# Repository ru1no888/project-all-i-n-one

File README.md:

# ระบบอุปกรณ์สวมใส่ติดตามสัญญาณชีพสุขภาพและเว็บแอปพลิเคชันบริหารจัดการคิวผู้ป่วยนอก
### (Hospital Queue Patient Portal & Smartwatch Health Monitoring)

---

## 📌 บทนำและภาพรวมโครงงาน (Overview)
โครงงานนี้เป็นการวิจัยและพัฒนานวัตกรรมระบบอุปกรณ์สวมใส่อัจฉริยะ (Smartwatch) ร่วมกับเว็บแอปพลิเคชันบริหารจัดการคิวผู้ป่วยนอกของโรงพยาบาล เพื่อยกระดับความปลอดภัยของผู้ป่วยในระหว่างรอรับการตรวจรักษา โดยระบบสามารถ:
1. **ติดตามสัญญาณชีพแบบเรียลไทม์ (Continuous Vital Signs Monitoring):** วัดอัตราการเต้นของหัวใจ (Heart Rate) และระดับความอิ่มตัวของออกซิเจนในเลือด ($SpO_2$) พร้อมคำนวณดัชนีช็อก (Shock Index: $SI = \frac{HR}{SBP}$) เพื่อประเมินภาวะวิกฤตของผู้ป่วย
2. **ตรวจจับอุบัติเหตุการหกล้ม (Multi-Stage Fall Detection):** ตรวจจับสภาวะการตกอิสระ (Free-fall), แรงกระแทก (Impact $SVM > 2.5g$) และสภาวะแน่นิ่งผิดปกติ (Inactivity) ด้วยเซนเซอร์ IMU 6 แกน
3. **จัดลำดับความเร่งด่วนของคิวอัตโนมัติ (Dynamic Queue Prioritization):** คัดกรองและปรับลำดับคิวผู้ป่วยตามหลักเกณฑ์ฉุกเฉิน ESI Version 4 ผ่านระบบ AI Triage เมื่อพบสัญญาณชีพวิกฤต
4. **แจ้งเตือนและส่งข้อมูลแบบทันที (Realtime Communication):** ส่งสัญญาณเตือนไปยังห้องพยาบาลและบุคลากรทางการแพทย์ผ่าน WebSockets ทันทีที่มีเหตุฉุกเฉิน

---

## 📁 โครงสร้างโฟลเดอร์ภายในโปรเจกต์ (Repository Structure)

```text
├── 01_เล่มรายงานโครงงาน_Thesis/
│   ├── เล่มรายงานโครงงาน_ฉบับสมบูรณ์_FINAL_v3_IEEE.docx    # เล่มรายงานโครงงานฉบับสมบูรณ์ (ฟอร์แมต IEEE มทร.อีสาน ขอนแก่น)
│   ├── เล่มรายงานโครงงาน_ฉบับสมบูรณ์_FINAL_v3_IEEE.pdf     # ไฟล์ PDF เล่มสมบูรณ์ (103 หน้า พร้อมตรวจ/พิมพ์)
│   ├── ECP-P01_แบบร่างโครงงานวิศวกรรมคอมพิวเตอร์_ฉบับปรับปรุงสมบูรณ์_v14.docx # แบบร่างข้อเสนอโครงงาน (Proposal v14)
│   ├── ECP-P01_แบบร่างโครงงานวิศวกรรมคอมพิวเตอร์_ฉบับปรับปรุงสมบูรณ์_v14.pdf  # ไฟล์ PDF แบบร่างโครงงาน (20 หน้าเต็ม)
│   └── ร่างเดิมและไฟล์สำรอง_Archive/                     # โฟลเดอร์สำรองไฟล์ดราฟต์เดิมทั้งหมดอย่างปลอดภัย
│
├── 02_ฮาร์ดแวร์และวงจร_Hardware/
│   ├── smartwatch_component_pinouts.html                 # ผังการต่อสาย Pinout และวงจรเซนเซอร์แบบ Interactive Web
│   ├── component_pinouts/                                # แผนภาพ Pinout รายชิ้นส่วน
│   ├── pcb_design/                                       # ไฟล์ออกแบบแผ่นวงจรพิมพ์ PCB (KiCad / EasyEDA)
│   └── pcb_design.zip                                    # ไฟล์บีบอัดสำหรับส่งโรงงานผลิต PCB (Gerber Files)
│
├── 03_ซอร์สโค้ดและเว็บแอป_SourceCode/
│   ├── repo_README.md                                    # เอกสารคู่มือการติดตั้งและการรัน Frontend Web App
│   ├── repo_ARCHITECTURE.md                              # สถาปัตยกรรมระบบ Frontend & Backend API Spec
│   ├── repo_package.json                                 # รายการ Dependencies (Next.js 14, React, Tailwind CSS)
│   ├── repo_patient-api.ts                               # API Client Module สำหรับเชื่อมต่อระบบโรงพยาบาล
│   ├── repo_types.ts                                     # TypeScript Interface สำหรับ Patient, Queue, Vital Signs
│   └── repo_mock_backend.py                              # สคริปต์จำลองเซิร์ฟเวอร์ Mock API สำหรับการทดสอบระบบ
│
├── 04_ไฟล์ข้อมูลและเครื่องมือเสริม_Assets_Tools/
│   ├── extracted_assets/                                 # รูปภาพและกราฟิกประกอบที่ใช้ในเอกสาร
│   ├── extracted_ch4_images/                             # ภาพผลการทดลองและการทดสอบระบบในบทที่ 4
│   ├── logo/                                             # ตราสัญลักษณ์มหาวิทยาลัยเทคโนโลยีราชมงคลอีสาน
│   └── build_full_thesis.py                              # สคริปต์สำหรับบิวด์และจัดรูปแบบรูปเล่มอัตโนมัติ
│
├── AGENTS.md                                             # ข้อกำหนดและแนวทางสำหรับ AI Assistant
├── GEMINI.md                                             # กฎระเบียบข้อบังคับและ Memory Protocol ประจำโปรเจกต์
├── PROJECT_MEMORY.md                                     # บันทึกความจำระยะยาว ประวัติการพัฒนา และข้อสรุปงาน
└── README.md                                             # เอกสารภาพรวมโปรเจกต์ (ไฟล์นี้)
```

---

## 🛠️ รายละเอียดสเปกฮาร์ดแวร์และเซนเซอร์ (Hardware Specifications)

| ส่วนประกอบ (Component) | รายละเอียด (Specification) | ฟังก์ชันการทำงาน |
|---|---|---|
| **MCU Controller** | Seeed Studio XIAO ESP32-C3 | หน่วยประมวลผลหลัก รองรับ Wi-Fi 2.4GHz และ BLE 5.0 |
| **Biometric Sensor** | MAX32664 Biometric Hub + MAX30102 PPG | ตรวจวัด Pulse Rate และ $SpO_2$ ด้วยความแม่นยำสูง |
| **Motion Sensor** | MPU-6050 (6-Axis Accel + Gyro) | ตรวจจับการเคลื่อนไหวและการหกล้ม 3 ขั้นตอน (SVM Analysis) |
| **Power Management** | TP4056 + แบตเตอรี่ LiPo 3.7V (500mAh) | วงจรชาร์จแบตเตอรี่ พร้อมวงจรแบ่งแรงดันวัดระดับแบตเตอรี่ |
| **Display** | จอแสดงผล OLED 0.96 นิ้ว (I2C) | แสดงผลอัตราเต้นหัวใจ, ออกซิเจนในเลือด และสถานะคิว |

---

## 💻 เทคโนโลยีฝั่งเว็บแอปพลิเคชัน (Software Stack)
- **Frontend Framework:** Next.js (App Router), React 18, TypeScript
- **Styling & UI:** Tailwind CSS, Lucide Icons, Headless UI
- **Database & Realtime:** Google Cloud Firestore, WebSockets
- **Deployment:** Vercel / Docker Container

---

## 👥 ผู้จัดทำโครงงาน (Contributors)
- **นายปรเมศว์ เดนนิส โฮค อาร์ริงตัน** (Mr. Porramet Dennis Hoke Arrington)
- **นายธนกร สุภาวรรณชัย** (Mr. Thanakorn Suphawanchai)

**สาขาวิชาวิศวกรรมคอมพิวเตอร์ คณะวิศวกรรมศาสตร์**  
**มหาวิทยาลัยเทคโนโลยีราชมงคลอีสาน วิทยาเขตขอนแก่น**  
**อาจารย์ที่ปรึกษาโครงงาน:** อาจารย์อรินธร เจษฎาเมธาขจร  
**ปีการศึกษา:** 2568 (Academic Year 2025)

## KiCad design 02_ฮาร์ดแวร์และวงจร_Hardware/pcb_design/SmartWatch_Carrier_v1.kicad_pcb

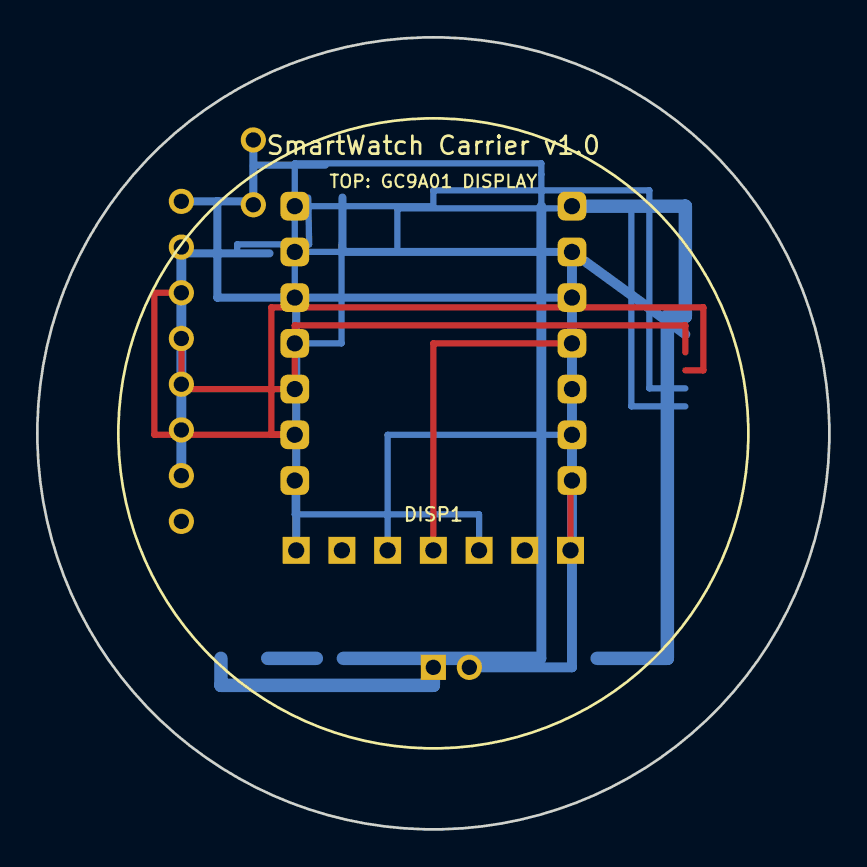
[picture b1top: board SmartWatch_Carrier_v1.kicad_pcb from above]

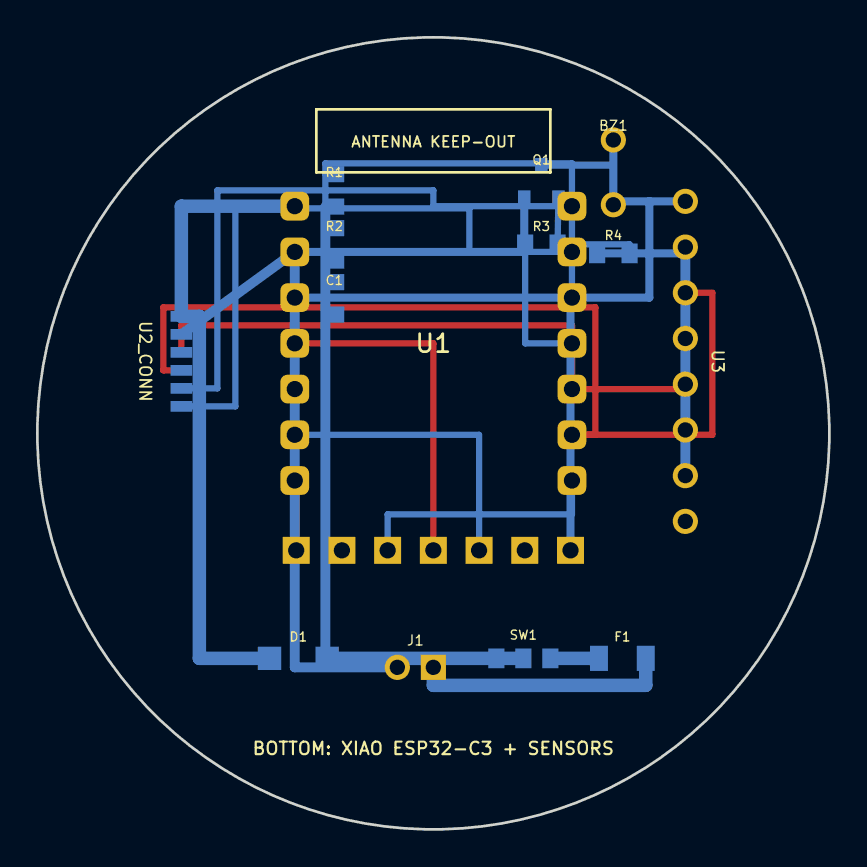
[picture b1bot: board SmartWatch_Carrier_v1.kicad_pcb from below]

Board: 2 copper layers, 44.0 x 44.0 mm, 15 parts (14 on the bottom side), 17 nets.

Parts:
BZ1: Buzzer_9x5.5mm
C1: C_0805_2012Metric
D1: D_SMA
DISP1: PinHeader_1x07_P2.54mm_Vertical
F1: R_1206_3216Metric
J1: JST_PH_B2B-PH-K_1x02_P2.00mm_Vertical
Q1: SOT-23
R1, R2, R3, R4: R_0805_2012Metric
SW1: SW_SPDT_PCM12
U1: Seeed_XIAO
U2_CONN: JST_SH_BM06B-SRSS-TB_1x06-1MP_P1.00mm_Vertical
U3: PinHeader_1x08_P2.54mm_Vertical

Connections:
3V3_SYS: BZ1.1, DISP1.1, U1.12, U3.1
5V_SYS: D1.2, U1.14, U2_CONN.1
ADC_BAT: C1.1, R1.2, R2.1, U1.3
BAT_SW+: R1.1, SW1.2
BUZZER_CTL: R3.1, U1.4
BUZZER_NEG: BZ1.2, Q1.3
GND_SYS: C1.2, DISP1.2, DISP1.6, J1.2, Q1.2, R2.2, R4.2, U1.13, U2_CONN.2, U3.2, U3.7
HUB_MFIO: U1.1, U2_CONN.5
HUB_RESET: U1.2, U2_CONN.6
I2C_SCL: U1.6, U2_CONN.4, U3.3
I2C_SDA: U1.5, U2_CONN.3, U3.4
Q1_BASE: Q1.1, R3.2, R4.1
SW_IN: F1.2, SW1.1
TFT_DC: DISP1.5, U1.7
TFT_MOSI: DISP1.4, U1.11
TFT_RST: DISP1.7, U1.8
TFT_SCK: DISP1.3, U1.9
